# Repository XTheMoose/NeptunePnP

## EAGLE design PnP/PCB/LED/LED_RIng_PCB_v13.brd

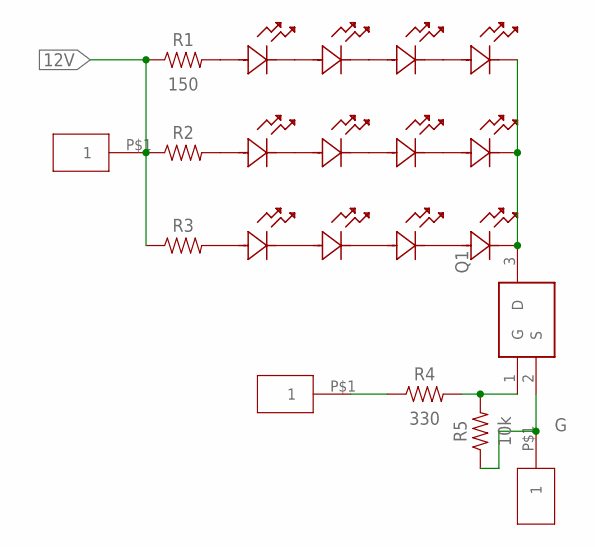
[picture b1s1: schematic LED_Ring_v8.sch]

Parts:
LED5, LED6, LED7, LED8, LED9, LED10, LED11, LED12, LED13, LED14, LED15, LED16: GW_JTLMS1.EM-GWH4-XX53-1-60-R3LED_SMT-GWJTLMS1.EM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; LED_SMT-GWJTLMS1.EM_AOS
Q1: IRLML6244TRPBF; SOT95P237X112-3N
R1: 150; RESC1005X40
R2, R3: R-US_CHIP-0402(1005-METRIC); RESC1005X40
R4: 330; RESC1005X40
R5: 10k; RESC1005X40
U$1, U$2, U$3: SOLDER_PAD_HOLE

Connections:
12V: R1.1, R2.1, R3.1, U$1.P$1
G: Q1.2 (S), R5.1, U$2.P$1
GND: LED8.1, LED12.1, LED16.1, Q1.3 (D)
unnamed: Q1.1 (G), R4.2, R5.2
unnamed: R4.1, U$3.P$1
unnamed: LED5.1, LED6.2
unnamed: LED6.1, LED7.2
unnamed: LED7.1, LED8.2
unnamed: LED9.1, LED10.2
unnamed: LED10.1, LED11.2
unnamed: LED11.1, LED12.2
unnamed: LED13.1, LED14.2
unnamed: LED14.1, LED15.2
unnamed: LED15.1, LED16.2
unnamed: LED13.2, R1.2
unnamed: LED9.2, R2.2
unnamed: LED5.2, R3.2

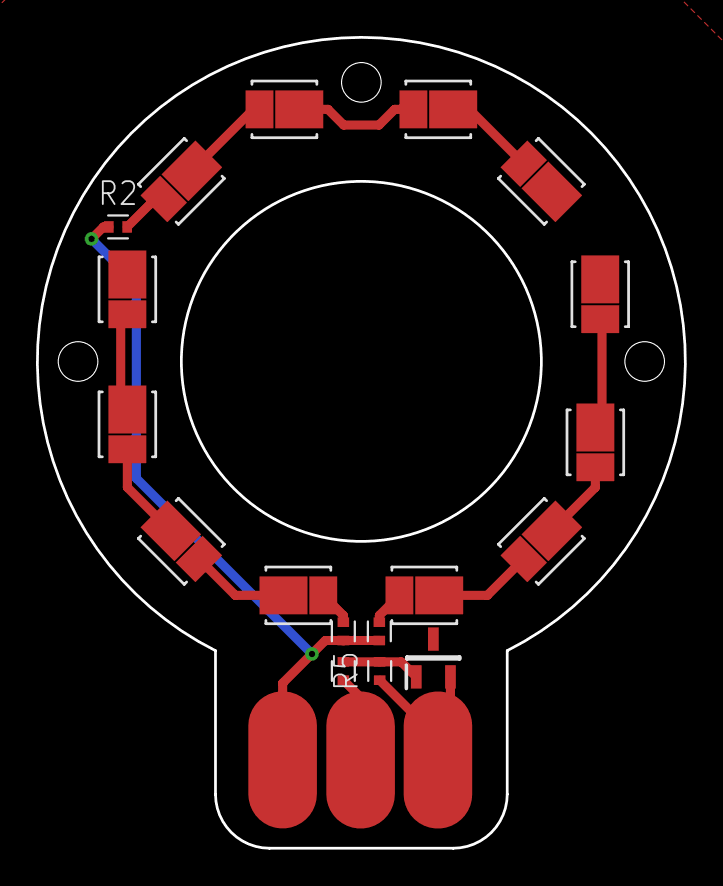
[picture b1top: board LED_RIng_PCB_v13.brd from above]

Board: 2 copper layers, 36.0 x 45.0 mm, 21 parts (0 on the bottom side), 17 nets.

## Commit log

2025-04-08 Commit Marlin from Forked Repository
2025-04-08 Upload CAD files for PnP
2025-04-08 openpnp .xml uploads
2025-04-09 Initialize Script Workspace
2025-04-10 Test Job

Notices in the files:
parts and their libraries:
COPYRIGHT: Copyright (C) 2025 Ultra Librarian. All rights reserved.
